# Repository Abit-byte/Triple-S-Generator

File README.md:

# Triple-S Generator
Un générateur de fonctions analogique compact, construit autour de l'amplificateur opérationnel TL072IP, capable de produire des signaux sinusoïdal, en dent de scie et carré.

---

### Caractéristiques :
- Trois formes d'onde simultanées : sortie sinusoïdale, dent de scie et carrée, sélectionnables via les commandes en façade
- Large plage de fréquences : condensateurs de calibrage commutables (3.3µF / 33nF / 330pF) couvrant environ 1.5 Hz à 150 kHz
- L'option de modifier le temps de montée et de descente, l'amplitude et la composante continue du signal avec des potentiomètres
- Alimentation symétrique ±9V pour des signaux de sortie centrés et propres
- Construction en traversant (THT) avec des composants largement disponibles (TL072IP, diodes 1N4148, composants passifs standards)
- PCB 2 couches avec plan de masse en cuivre pour réduire le bruit
- Connecteurs à vis pour l'alimentation et la sortie signal

### Détails de conception :
- U1 gère l'oscillateur à trigger de Schmitt et l'étage intégrateur (génération du carré et de la dent de scie)
- U2 gère la mise en forme du signal sinusoïdal et le buffer de sortie
- Le réseau de diodes (D1–D4) assure la mise en forme du signal sinusoïdal
- Des commutateurs SP3T permettent de sélectionner la forme d'onde et la plage de fréquence
- Conçu et routé sous KiCad, fabriqué via JLCPCB

---

## Photos de résultats

> Vous pouvez les trouver aussi dans la dossier *Photos-of-final-result*.

| Schémas | PCB |
| :-----------: | :-----------: |
|  |  |

---

> [!NOTE]
> Une Intelligence Artificielle a été utilisée uniquement pour rédiger ce texte README.

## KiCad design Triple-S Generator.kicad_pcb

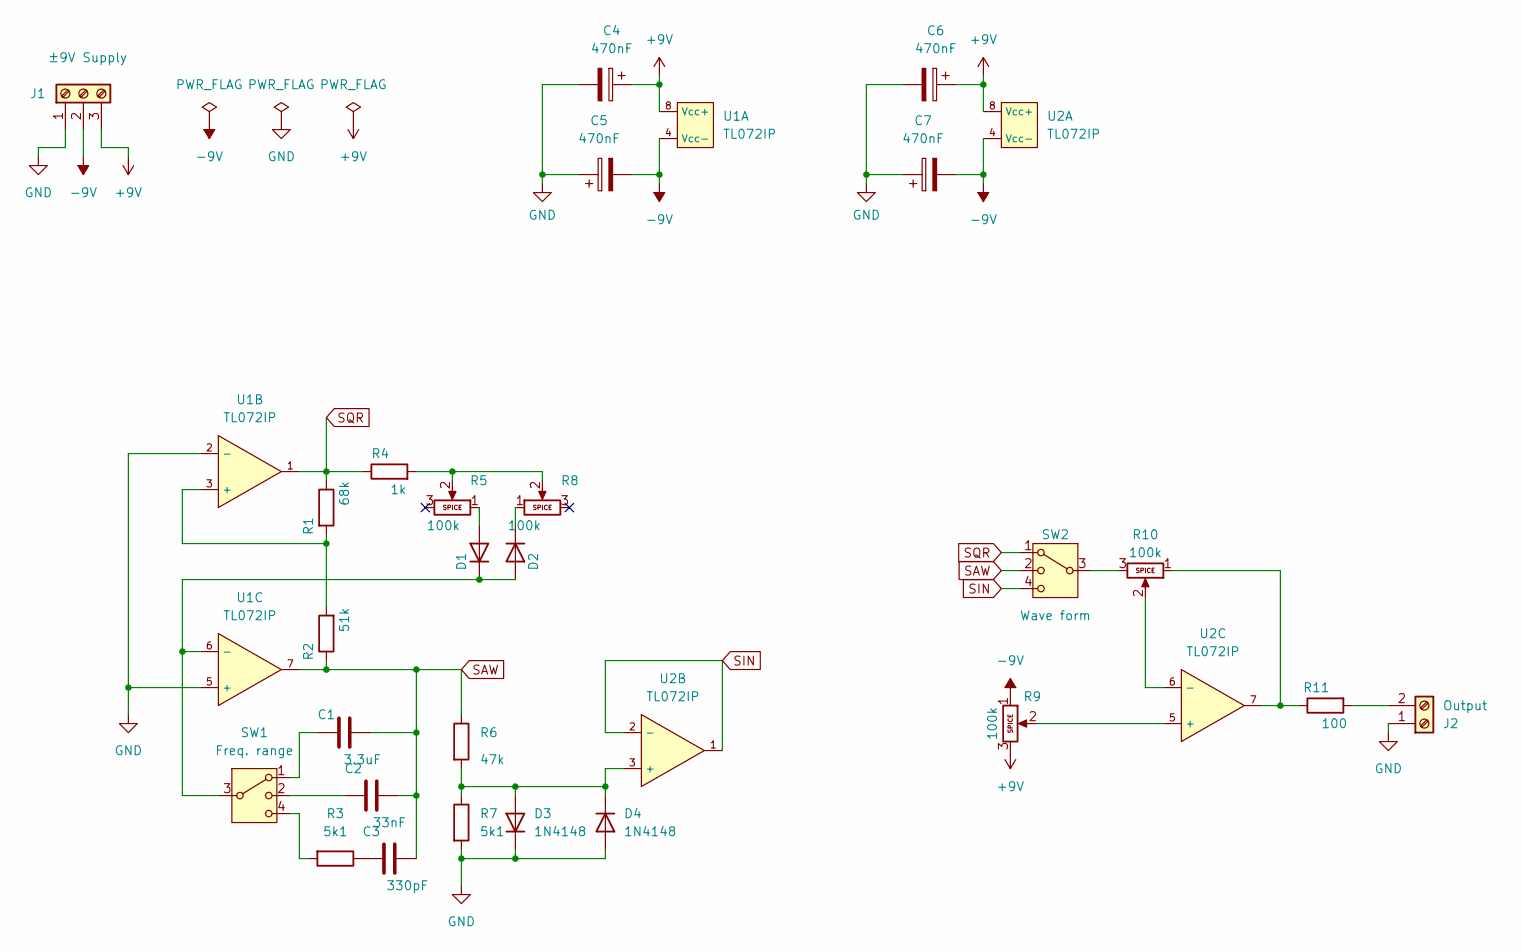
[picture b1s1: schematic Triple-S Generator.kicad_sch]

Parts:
C1: 3.3uF; C_Rect_L16.5mm_W7.0mm_P15.00mm_MKT
C2: 33nF; C_Disc_D4.3mm_W1.9mm_P5.00mm
C3: 330pF; C_Disc_D4.3mm_W1.9mm_P5.00mm
C4, C5, C6, C7: 470nF; CP_Radial_D6.3mm_P2.50mm
D1, D2, D3, D4: 1N4148; D_DO-35_SOD27_P7.62mm_Horizontal
J1: ±9V Supply; Terminal Block 3 pos
J2: Output; Terminal Block 2 pos
R1: 68k; R_Axial_DIN0207_L6.3mm_D2.5mm_P7.62mm_Horizontal
R2: 51k; R_Axial_DIN0207_L6.3mm_D2.5mm_P7.62mm_Horizontal
R3, R7: 5k1; R_Axial_DIN0207_L6.3mm_D2.5mm_P7.62mm_Horizontal
R4: 1k; R_Axial_DIN0207_L6.3mm_D2.5mm_P7.62mm_Horizontal
R5, R8, R9, R10: 100k; Potentiometer_Alpha_RD901F-40-00D_Single_Vertical
R6: 47k; R_Axial_DIN0207_L6.3mm_D2.5mm_P7.62mm_Horizontal
R11: 100; R_Axial_DIN0207_L6.3mm_D2.5mm_P7.62mm_Horizontal
SW1: Freq. range; Switch SP3T
SW2: Wave form; Switch SP3T
U1, U2: TL072IP; 8-Dip

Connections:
+9V: C4.1, C6.1, J1.3, R9.3, U1.8 (Vcc+), U2.8 (Vcc+)
-9V: C5.2, C7.2, J1.2, R9.1, U1.4 (Vcc-), U2.4 (Vcc-)
GND: C4.2, C5.1, C6.2, C7.1, D3.1 (K), D4.2 (A), J1.1, J2.1, R7.2, U1.2 (-), U1.5 (+)
unnamed: C1.1, SW1.1
unnamed: C2.1, SW1.2
unnamed: C3.1, R3.1
unnamed: D1.2 (A), R5.1
unnamed: D1.1 (K), D2.2 (A), SW1.3, U1.6 (-)
unnamed: D2.1 (K), R8.1
unnamed: D3.2 (A), D4.1 (K), R6.2, R7.1, U2.3 (+)
unnamed: J2.2, R11.2
unnamed: R3.2, SW1.4
unnamed: R4.2, R5.2, R8.2
unnamed: R10.1, R11.1, U2.7
unnamed: R10.3, SW2.3
unnamed: R1.2, R2.2, U1.3 (+)
unnamed: R9.2, U2.5 (+)
unnamed: R10.2, U2.6 (-)
SAW: C1.2, C2.2, C3.2, R2.1, R6.1, SW2.2, U1.7
SIN: SW2.4, U2.1, U2.2 (-)
SQR: R1.1, R4.1, SW2.1, U1.1

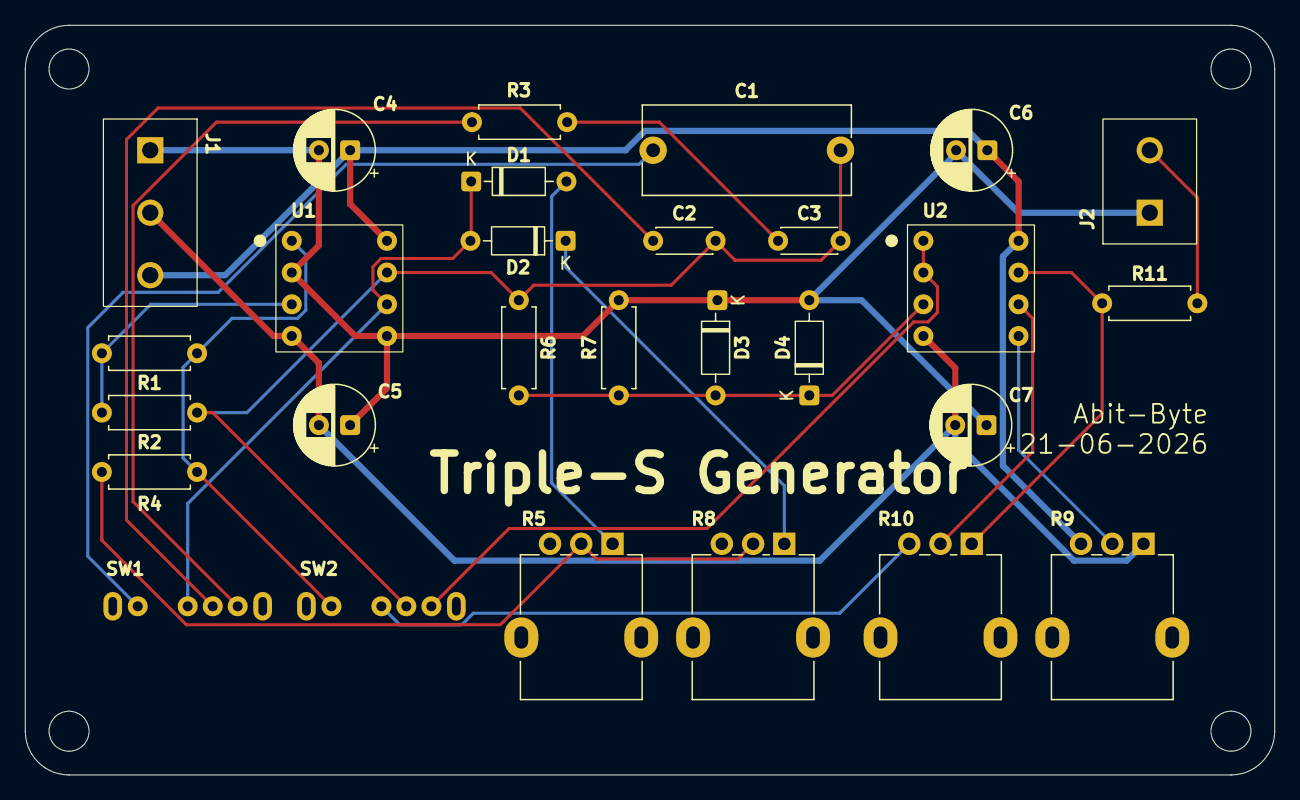
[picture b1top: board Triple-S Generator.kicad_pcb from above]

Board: 2 copper layers, 100.0 x 60.0 mm, 28 parts (0 on the bottom side), 21 nets.

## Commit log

2026-06-30 Post to GitHub
2026-06-30 Photos update
2026-06-30 Update image references in README
